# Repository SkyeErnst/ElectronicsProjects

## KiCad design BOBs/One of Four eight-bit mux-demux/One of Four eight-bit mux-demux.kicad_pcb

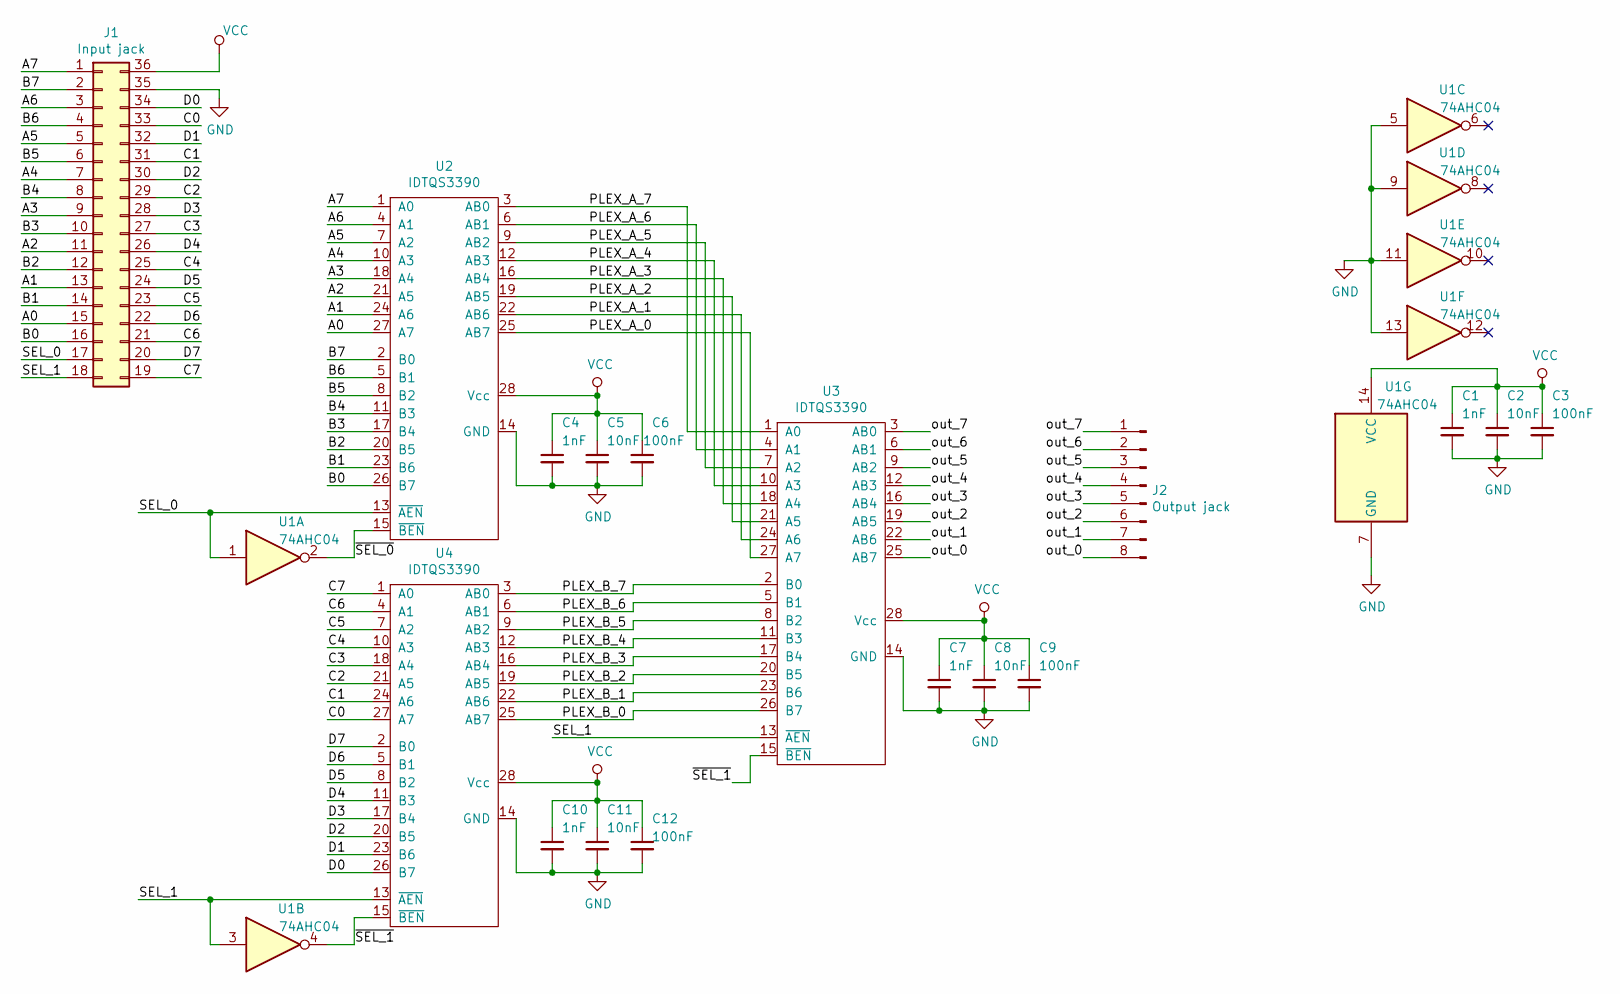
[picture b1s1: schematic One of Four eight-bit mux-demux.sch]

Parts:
C1, C4, C7, C10: 1nF; C_0805_2012Metric_Pad1.15x1.40mm_HandSolder
C2, C5, C8, C11: 10nF; C_0805_2012Metric_Pad1.15x1.40mm_HandSolder
C3, C6, C9, C12: 100nF; C_0805_2012Metric_Pad1.15x1.40mm_HandSolder
J1: Input jack; PinHeader_2x18_P2.54mm_Vertical
J2: Output jack; PinHeader_1x08_P2.54mm_Vertical
U1: 74AHC04; SOIC-14_3.9x8.7mm_P1.27mm
U2, U3, U4: IDTQS3390; SSOP-28_3.9x9.9mm_P0.635mm

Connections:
/A0: J1.15, U2.27 (A7)
/A1: J1.13, U2.24 (A6)
/A2: J1.11, U2.21 (A5)
/A3: J1.9, U2.18 (A4)
/A4: J1.7, U2.10 (A3)
/A5: J1.5, U2.7 (A2)
/A6: J1.3, U2.4 (A1)
/A7: J1.1, U2.1 (A0)
/B0: J1.16, U2.26 (B7)
/B1: J1.14, U2.23 (B6)
/B2: J1.12, U2.20 (B5)
/B3: J1.10, U2.17 (B4)
/B4: J1.8, U2.11 (B3)
/B5: J1.6, U2.8 (B2)
/B6: J1.4, U2.5 (B1)
/B7: J1.2, U2.2 (B0)
/C0: J1.33, U4.27 (A7)
/C1: J1.31, U4.24 (A6)
/C2: J1.29, U4.21 (A5)
/C3: J1.27, U4.18 (A4)
/C4: J1.25, U4.10 (A3)
/C5: J1.23, U4.7 (A2)
/C6: J1.21, U4.4 (A1)
/C7: J1.19, U4.1 (A0)
/D0: J1.34, U4.26 (B7)
/D1: J1.32, U4.23 (B6)
/D2: J1.30, U4.20 (B5)
/D3: J1.28, U4.17 (B4)
/D4: J1.26, U4.11 (B3)
/D5: J1.24, U4.8 (B2)
/D6: J1.22, U4.5 (B1)
/D7: J1.20, U4.2 (B0)
/PLEX_A_0: U2.25 (AB7), U3.27 (A7)
/PLEX_A_1: U2.22 (AB6), U3.24 (A6)
/PLEX_A_2: U2.19 (AB5), U3.21 (A5)
/PLEX_A_3: U2.16 (AB4), U3.18 (A4)
/PLEX_A_4: U2.12 (AB3), U3.10 (A3)
/PLEX_A_5: U2.9 (AB2), U3.7 (A2)
/PLEX_A_6: U2.6 (AB1), U3.4 (A1)
/PLEX_A_7: U2.3 (AB0), U3.1 (A0)
/PLEX_B_0: U3.26 (B7), U4.25 (AB7)
/PLEX_B_1: U3.23 (B6), U4.22 (AB6)
/PLEX_B_2: U3.20 (B5), U4.19 (AB5)
/PLEX_B_3: U3.17 (B4), U4.16 (AB4)
/PLEX_B_4: U3.11 (B3), U4.12 (AB3)
/PLEX_B_5: U3.8 (B2), U4.9 (AB2)
/PLEX_B_6: U3.5 (B1), U4.6 (AB1)
/PLEX_B_7: U3.2 (B0), U4.3 (AB0)
/SEL_0: J1.17, U1.1, U2.13 (~AEN)
/SEL_1: J1.18, U1.3, U3.13 (~AEN), U4.13 (~AEN)
/out_0: J2.8, U3.25 (AB7)
/out_1: J2.7, U3.22 (AB6)
/out_2: J2.6, U3.19 (AB5)
/out_3: J2.5, U3.16 (AB4)
/out_4: J2.4, U3.12 (AB3)
/out_5: J2.3, U3.9 (AB2)
/out_6: J2.2, U3.6 (AB1)
/out_7: J2.1, U3.3 (AB0)
/~SEL_0: U1.2, U2.15 (~BEN)
/~SEL_1: U1.4, U3.15 (~BEN), U4.15 (~BEN)
GND: C1.2, C2.2, C3.2, C4.2, C5.2, C6.2, C7.2, C8.2, C9.2, C10.2, C11.2, C12.2, J1.35, U1.5, U1.7 (GND), U1.9, U1.11, U1.13, U2.14 (GND), U3.14 (GND), U4.14 (GND)
VCC: C1.1, C2.1, C3.1, C4.1, C5.1, C6.1, C7.1, C8.1, C9.1, C10.1, C11.1, C12.1, J1.36, U1.14 (VCC), U2.28 (Vcc), U3.28 (Vcc), U4.28 (Vcc)

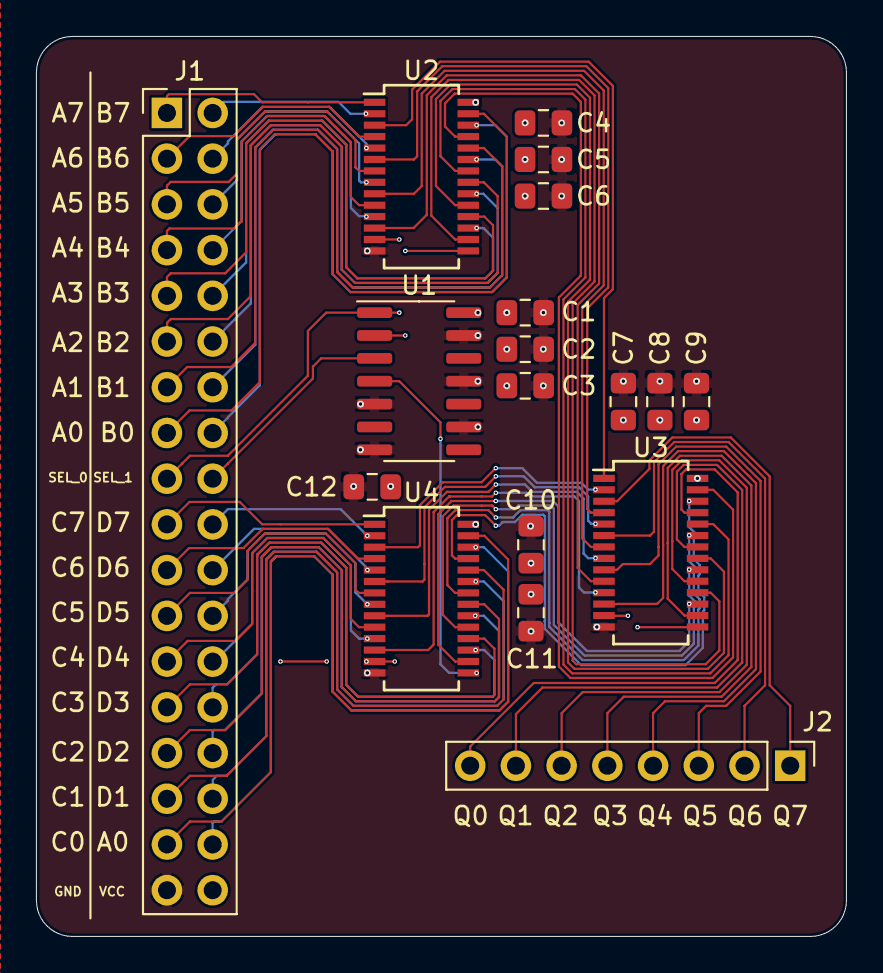
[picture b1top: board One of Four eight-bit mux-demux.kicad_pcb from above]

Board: 4 copper layers, 45.0 x 50.0 mm, 18 parts (0 on the bottom side), 62 nets.

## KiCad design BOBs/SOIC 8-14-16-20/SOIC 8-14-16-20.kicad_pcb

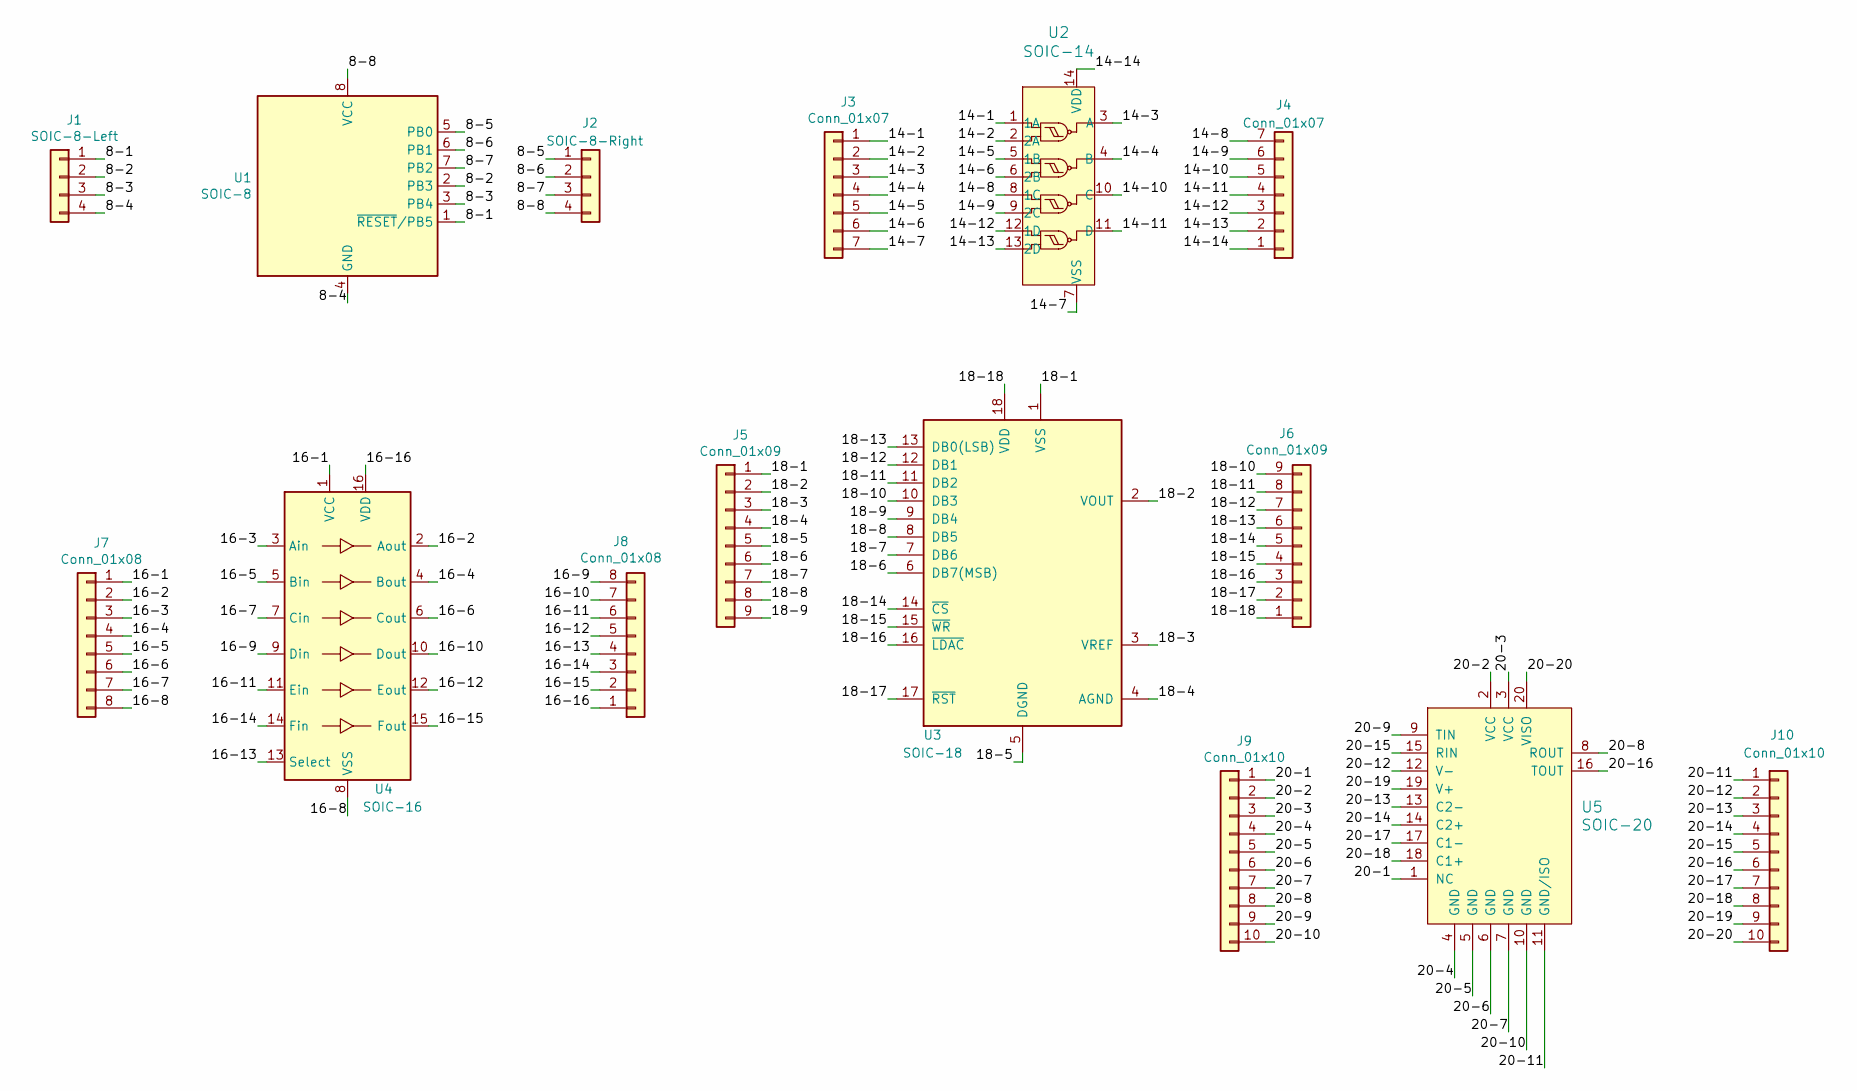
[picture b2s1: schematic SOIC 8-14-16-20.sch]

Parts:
J1: SOIC-8-Left; PinHeader_1x04_P2.54mm_Vertical
J2: SOIC-8-Right; PinHeader_1x04_P2.54mm_Vertical
J3, J4: Conn_01x07; PinHeader_1x07_P2.54mm_Vertical
J5, J6: Conn_01x09; PinHeader_1x09_P2.54mm_Vertical
J7, J8: Conn_01x08; PinHeader_1x08_P2.54mm_Vertical
J9, J10: Conn_01x10; PinHeader_1x10_P2.54mm_Vertical
U1: SOIC-8; SOIC-8_3.9x4.9mm_P1.27mm
U2: SOIC-14; SOIC-14_3.9x8.7mm_P1.27mm; MPN MC14093BDR2G; Digi-Key_PN MC14093BDR2GOSCT-ND
U3: SOIC-18; SOIC-18_W7.5mm
U4: SOIC-16; SOIC-16_3.9x9.9mm_P1.27mm
U5: SOIC-20; SOIC-20_W7.5mm; MPN ADM3251EARWZ; Digi-Key_PN ADM3251EARWZ-ND

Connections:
/8-1: J1.1, U1.1 (~RESET~/PB5)
/8-2: J1.2, U1.2 (PB3)
/8-3: J1.3, U1.3 (PB4)
/8-4: J1.4, U1.4 (GND)
/8-5: J2.1, U1.5 (PB0)
/8-6: J2.2, U1.6 (PB1)
/8-7: J2.3, U1.7 (PB2)
/8-8: J2.4, U1.8 (VCC)
/14-1: J3.1, U2.1 (1A)
/14-2: J3.2, U2.2 (2A)
/14-3: J3.3, U2.3 (A)
/14-4: J3.4, U2.4 (B)
/14-5: J3.5, U2.5 (1B)
/14-6: J3.6, U2.6 (2B)
/14-7: J3.7, U2.7 (VSS)
/14-8: J4.7, U2.8 (1C)
/14-9: J4.6, U2.9 (2C)
/14-10: J4.5, U2.10 (C)
/14-11: J4.4, U2.11 (D)
/14-12: J4.3, U2.12 (1D)
/14-13: J4.2, U2.13 (2D)
/14-14: J4.1, U2.14 (VDD)
/16-1: J7.1, U4.1 (VCC)
/16-2: J7.2, U4.2 (Aout)
/16-3: J7.3, U4.3 (Ain)
/16-4: J7.4, U4.4 (Bout)
/16-5: J7.5, U4.5 (Bin)
/16-6: J7.6, U4.6 (Cout)
/16-7: J7.7, U4.7 (Cin)
/16-8: J7.8, U4.8 (VSS)
/16-9: J8.8, U4.9 (Din)
/16-10: J8.7, U4.10 (Dout)
/16-11: J8.6, U4.11 (Ein)
/16-12: J8.5, U4.12 (Eout)
/16-13: J8.4, U4.13 (Select)
/16-14: J8.3, U4.14 (Fin)
/16-15: J8.2, U4.15 (Fout)
/16-16: J8.1, U4.16 (VDD)
/18-1: J5.1, U3.1 (VSS)
/18-2: J5.2, U3.2 (VOUT)
/18-3: J5.3, U3.3 (VREF)
/18-4: J5.4, U3.4 (AGND)
/18-5: J5.5, U3.5 (DGND)
/18-6: J5.6, U3.6 (DB7(MSB))
/18-7: J5.7, U3.7 (DB6)
/18-8: J5.8, U3.8 (DB5)
/18-9: J5.9, U3.9 (DB4)
/18-10: J6.9, U3.10 (DB3)
/18-11: J6.8, U3.11 (DB2)
/18-12: J6.7, U3.12 (DB1)
/18-13: J6.6, U3.13 (DB0(LSB))
/18-14: J6.5, U3.14 (~CS)
/18-15: J6.4, U3.15 (~WR)
/18-16: J6.3, U3.16 (~LDAC)
/18-17: J6.2, U3.17 (~RST)
/18-18: J6.1, U3.18 (VDD)
/20-1: J9.1, U5.1 (NC)
/20-2: J9.2, U5.2 (VCC)
/20-3: J9.3, U5.3 (VCC)
/20-4: J9.4, U5.4 (GND)
/20-5: J9.5, U5.5 (GND)
/20-6: J9.6, U5.6 (GND)
/20-7: J9.7, U5.7 (GND)
/20-8: J9.8, U5.8 (ROUT)
/20-9: J9.9, U5.9 (TIN)
/20-10: J9.10, U5.10 (GND)
/20-11: J10.1, U5.11 (GND/ISO)
/20-12: J10.2, U5.12 (V-)
/20-13: J10.3, U5.13 (C2-)
/20-14: J10.4, U5.14 (C2+)
/20-15: J10.5, U5.15 (RIN)
/20-16: J10.6, U5.16 (TOUT)
/20-17: J10.7, U5.17 (C1-)
/20-18: J10.8, U5.18 (C1+)
/20-19: J10.9, U5.19 (V+)
/20-20: J10.10, U5.20 (VISO)

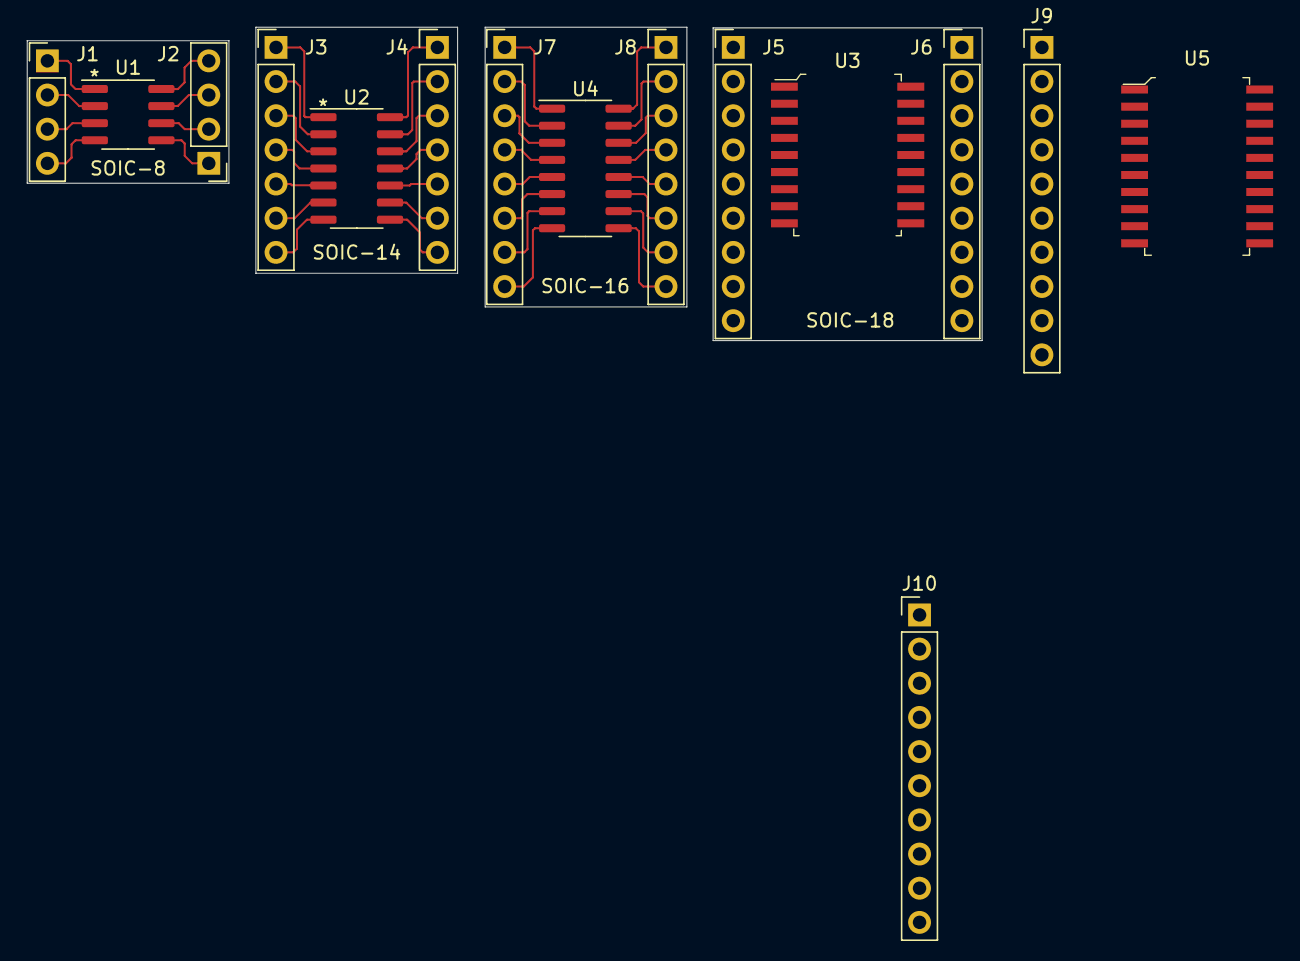
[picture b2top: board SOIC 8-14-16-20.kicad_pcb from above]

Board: 2 copper layers, 71.0 x 23.3 mm, 15 parts (0 on the bottom side), 76 nets.
